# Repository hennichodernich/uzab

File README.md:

# UZAB: Universal Zynq-7000 AD/DA Board
A KiCad project

Presented without any warranty

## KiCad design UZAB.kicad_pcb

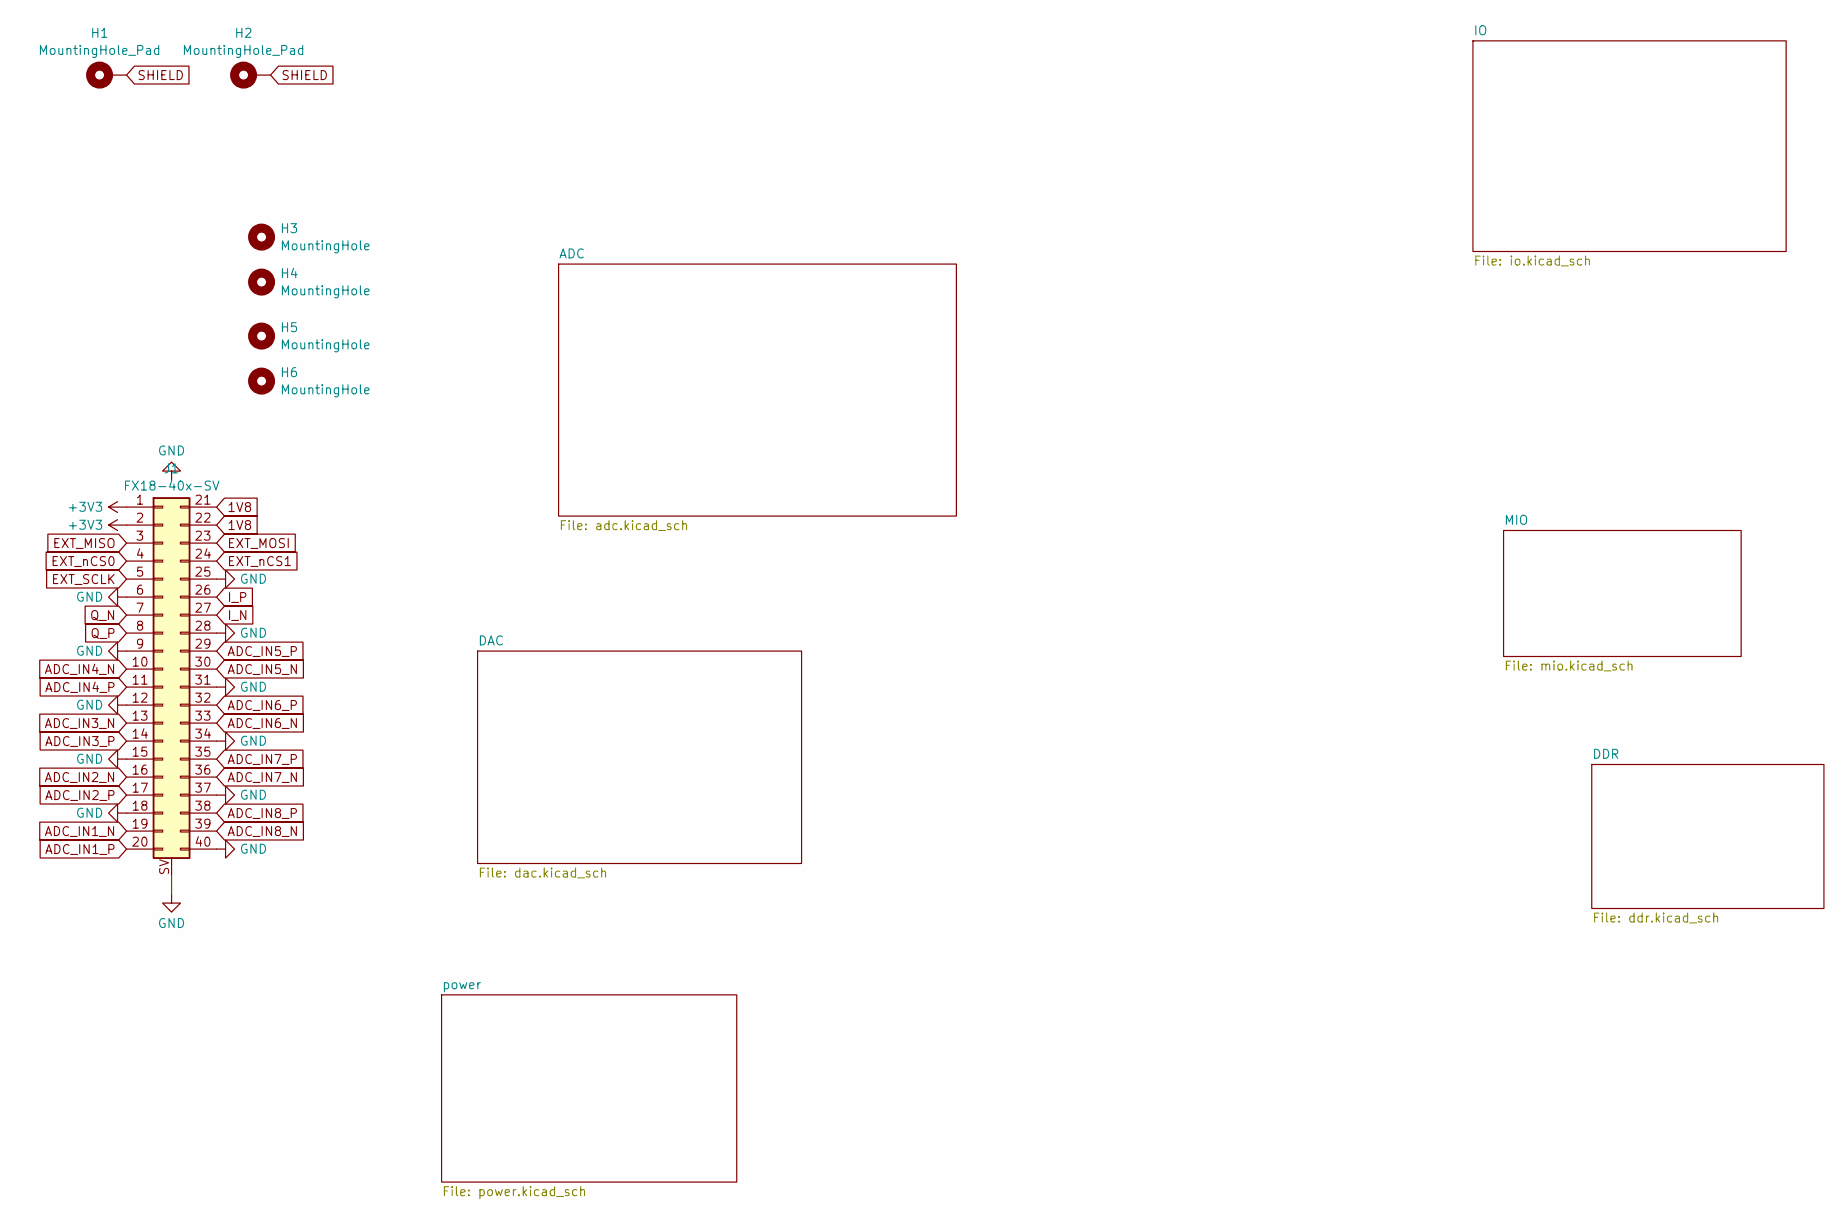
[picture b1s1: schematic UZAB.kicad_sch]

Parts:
H1, H2: MountingHole_Pad; MountingHole_3.2mm_M3_DIN965_Pad_TopBottom
H3, H4, H5, H6: MountingHole; MountingHole_3.2mm_M3_DIN965
J1: FX18-40x-SV; FX18-40P-0.8SV

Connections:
1V8: J1.21, J1.22; also elsewhere on the board
3V3: J1.1, J1.2; also elsewhere on the board
ADC_IN1_N: J1.19; also elsewhere on the board
ADC_IN1_P: J1.20; also elsewhere on the board
ADC_IN2_N: J1.16; also elsewhere on the board
ADC_IN2_P: J1.17; also elsewhere on the board
ADC_IN3_N: J1.13; also elsewhere on the board
ADC_IN3_P: J1.14; also elsewhere on the board
ADC_IN4_N: J1.10; also elsewhere on the board
ADC_IN4_P: J1.11; also elsewhere on the board
ADC_IN5_N: J1.30; also elsewhere on the board
ADC_IN5_P: J1.29; also elsewhere on the board
ADC_IN6_N: J1.33; also elsewhere on the board
ADC_IN6_P: J1.32; also elsewhere on the board
ADC_IN7_N: J1.36; also elsewhere on the board
ADC_IN7_P: J1.35; also elsewhere on the board
ADC_IN8_N: J1.39; also elsewhere on the board
ADC_IN8_P: J1.38; also elsewhere on the board
EXT_MISO: J1.3; also elsewhere on the board
EXT_MOSI: J1.23; also elsewhere on the board
EXT_SCLK: J1.5; also elsewhere on the board
EXT_nCS0: J1.4; also elsewhere on the board
EXT_nCS1: J1.24; also elsewhere on the board
GND: J1.6, J1.9, J1.12, J1.15, J1.18, J1.25, J1.28, J1.31, J1.34, J1.37, J1.40, J1.SV; also elsewhere on the board
I_N: J1.27; also elsewhere on the board
I_P: J1.26; also elsewhere on the board
Q_N: J1.7; also elsewhere on the board
Q_P: J1.8; also elsewhere on the board
SHIELD: H1.1, H2.1; also elsewhere on the board

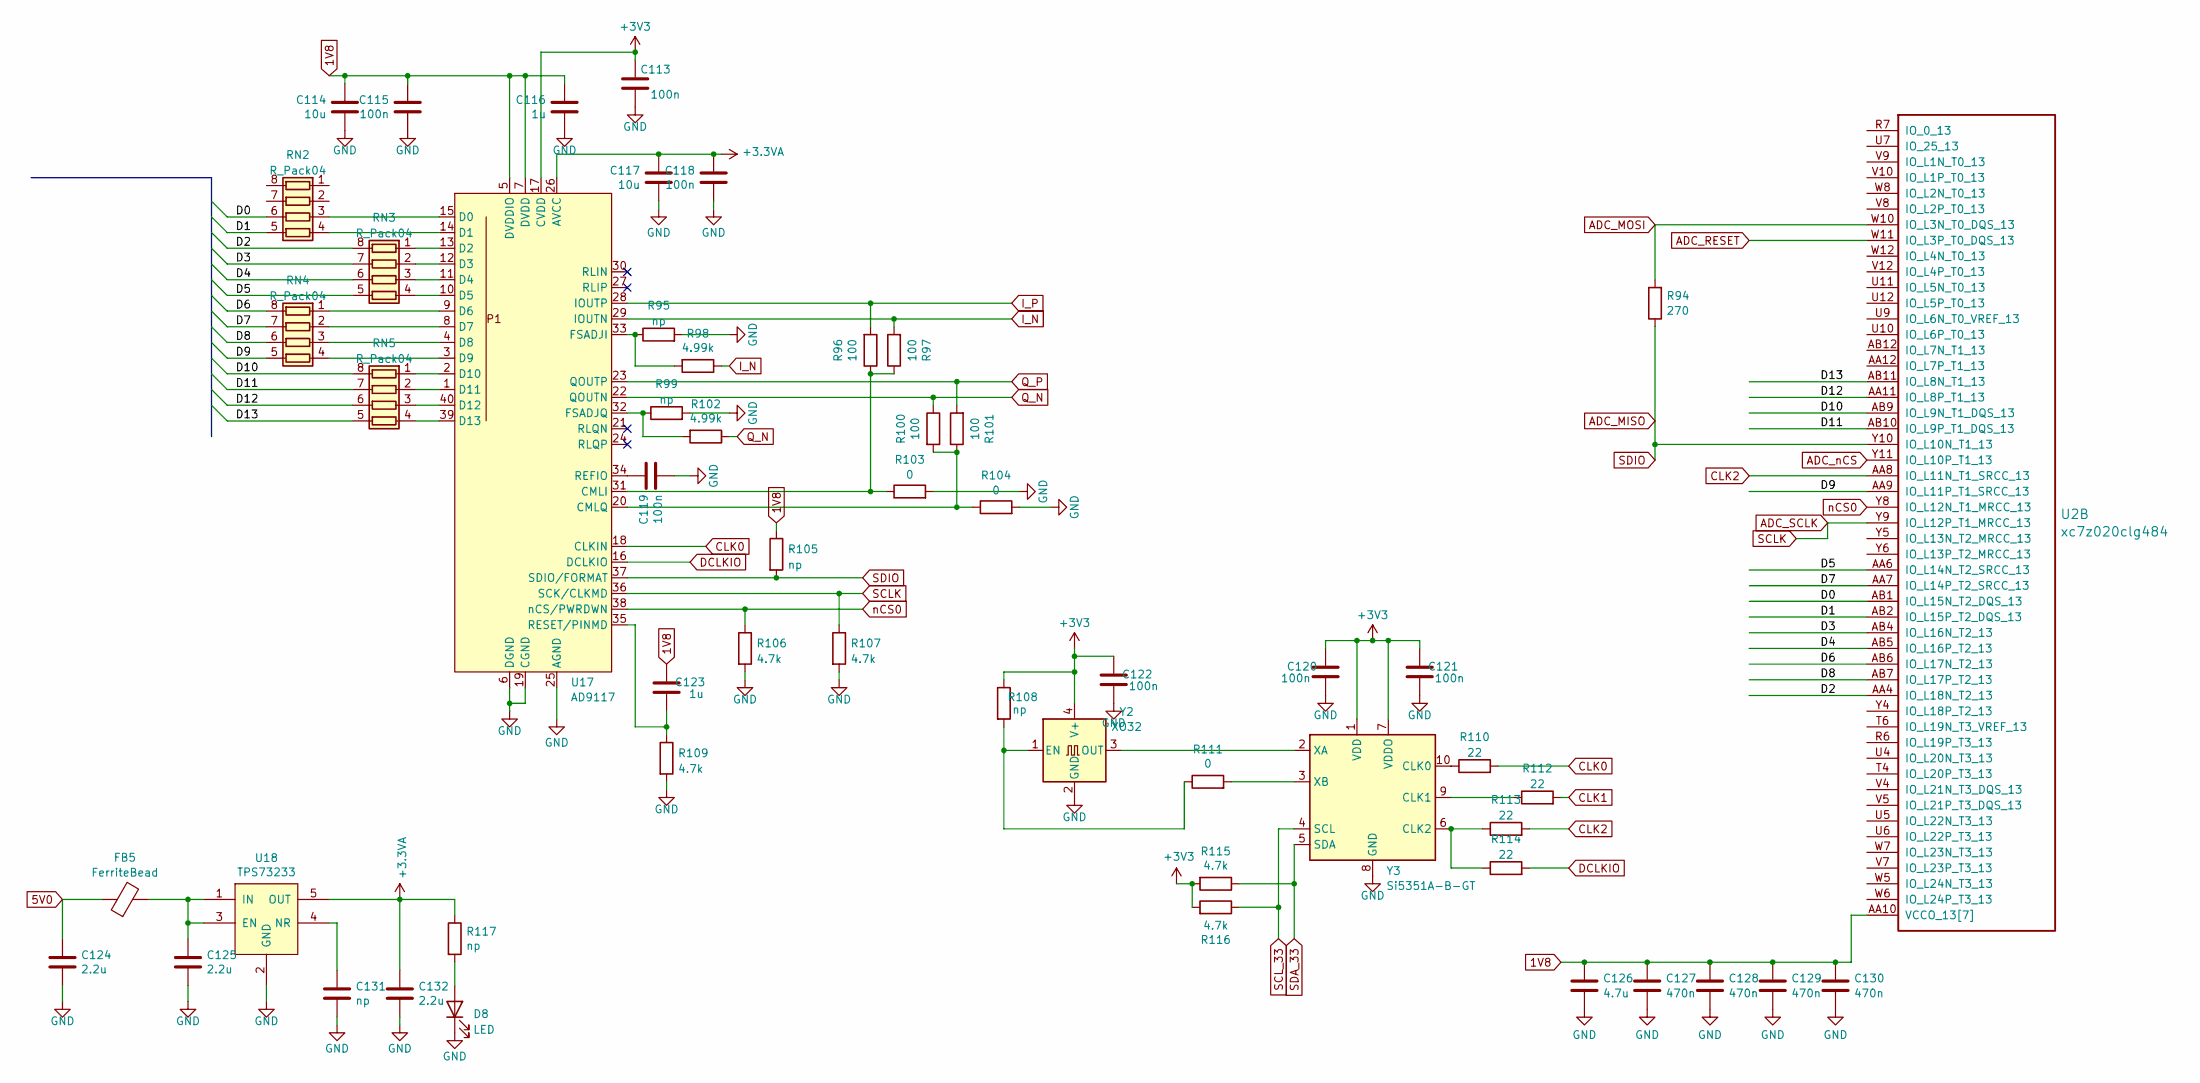
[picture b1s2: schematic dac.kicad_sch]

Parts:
C113, C115, C118, C119, C120, C121, C122: 100n; C_0402_1005Metric
C114, C117: 10u; C_0603_1608Metric
C116: 1u; C_0603_1608Metric
C123: 1u; C_0402_1005Metric
C124, C125, C132: 2.2u; C_0603_1608Metric
C126: 4.7u; C_0603_1608Metric
C127, C128, C129, C130: 470n; C_0201_BGA
C131: np; C_0402_1005Metric
D8: LED; LED_0603_1608Metric
FB5: FerriteBead; L_0603_1608Metric
R94: 270; R_0402_1005Metric
R95, R99, R105, R108: np; R_0402_1005Metric
R96, R97, R100, R101: 100; R_0603_1608Metric
R98, R102: 4.99k; R_0603_1608Metric
R103, R104, R111: 0; R_0402_1005Metric
R106, R107, R109, R115, R116: 4.7k; R_0402_1005Metric
R110, R112, R113, R114: 22; R_0402_1005Metric
R117: np; R_0603_1608Metric
RN2, RN3, RN4, RN5: R_Pack04; R_Array_Concave_4x0603
U2: xc7z020clg484; Xilinx_CLG484_CLG485
U17: AD9117; HVQFN-40-1EP_6x6mm_P0.5mm_EP4.1x4.1mm_ThermalVias
U18: TPS73233; SOT-23-5
Y2: XO32; Oscillator_SMD_EuroQuartz_XO32-4Pin_3.2x2.5mm
Y3: Si5351A-B-GT; MSOP-10_3x3mm_P0.5mm

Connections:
1V8: C114.1, C115.1, C116.1, C123.1, C126.1, C127.1, C128.1, C129.1, C130.1, R105.1, U2.AA10 (VCCO_13[7]), U2.AB3 (VCCO_13[7]), U2.T5 (VCCO_13[7]), U2.U8 (VCCO_13[7]), U2.V11 (VCCO_13[7]), U2.W4 (VCCO_13[7]), U2.Y7 (VCCO_13[7]), U17.5 (DVDDIO), U17.7 (DVDD); also elsewhere on the board
3V3: C113.1, C120.1, C121.1, C122.1, R108.1, R115.2, R116.2, U17.17 (CVDD), Y2.4 (V+), Y3.1 (VDD), Y3.7 (VDDO); also elsewhere on the board
5V0: C124.1, FB5.1; also elsewhere on the board
+3.3VA: C117.1, C118.1, C132.1, R117.1, U17.26 (AVCC), U18.5 (OUT)
/DAC/D0: RN2.6 (R3.2), U2.AB1 (IO_L15N_T2_DQS_13)
/DAC/D1: RN2.5 (R4.2), U2.AB2 (IO_L15P_T2_DQS_13)
/DAC/D2: RN3.8 (R1.2), U2.AA4 (IO_L18N_T2_13)
/DAC/D3: RN3.7 (R2.2), U2.AB4 (IO_L16N_T2_13)
/DAC/D4: RN3.6 (R3.2), U2.AB5 (IO_L16P_T2_13)
/DAC/D5: RN3.5 (R4.2), U2.AA6 (IO_L14N_T2_SRCC_13)
/DAC/D6: RN4.8 (R1.2), U2.AB6 (IO_L17N_T2_13)
/DAC/D7: RN4.7 (R2.2), U2.AA7 (IO_L14P_T2_SRCC_13)
/DAC/D8: RN4.6 (R3.2), U2.AB7 (IO_L17P_T2_13)
/DAC/D9: RN4.5 (R4.2), U2.AA9 (IO_L11P_T1_SRCC_13)
/DAC/D10: RN5.8 (R1.2), U2.AB9 (IO_L9N_T1_DQS_13)
/DAC/D11: RN5.7 (R2.2), U2.AB10 (IO_L9P_T1_DQS_13)
/DAC/D12: RN5.6 (R3.2), U2.AA11 (IO_L8P_T1_13)
/DAC/D13: RN5.5 (R4.2), U2.AB11 (IO_L8N_T1_13)
ADC_MISO: R94.1, R105.2, U2.Y10 (IO_L10N_T1_13), U17.37 (SDIO/FORMAT); also elsewhere on the board
ADC_MOSI: R94.2, U2.W10 (IO_L3N_T0_DQS_13); also elsewhere on the board
ADC_RESET: U2.W11 (IO_L3P_T0_DQS_13); also elsewhere on the board
ADC_SCLK: R107.1, U2.Y9 (IO_L12P_T1_MRCC_13), U17.36 (SCK/CLKMD); also elsewhere on the board
ADC_nCS: U2.Y11 (IO_L10P_T1_13); also elsewhere on the board
CLK0: R110.2, U17.18 (CLKIN)
CLK1: R112.2; also elsewhere on the board
CLK2: R113.2, U2.AA8 (IO_L11N_T1_SRCC_13)
DCLKIO: R114.2, U17.16 (DCLKIO)
GND: C113.2, C114.2, C115.2, C116.2, C117.2, C118.2, C119.2, C120.2, C121.2, C122.2, C124.2, C125.2, C126.2, C127.2, C128.2, C129.2, C130.2, C131.2, C132.2, D8.1 (K), R95.2, R99.2, R103.2, R104.2, R106.2, R107.2, R109.2, U17.6 (DGND), U17.19 (CGND), U17.25 (AGND), U17.41 (AGND), U18.2 (GND), Y2.2 (GND), Y3.8 (GND); also elsewhere on the board
I_N: R97.2, R98.1, U17.29 (IOUTN); also elsewhere on the board
I_P: R96.2, U17.28 (IOUTP); also elsewhere on the board
unnamed: D8.2 (A), R117.2
unnamed: RN2.3 (R3.1), U17.15 (D0)
unnamed: RN2.4 (R4.1), U17.14 (D1)
unnamed: RN3.1 (R1.1), U17.13 (D2)
unnamed: RN3.2 (R2.1), U17.12 (D3)
unnamed: RN3.3 (R3.1), U17.11 (D4)
unnamed: RN3.4 (R4.1), U17.10 (D5)
unnamed: RN4.1 (R1.1), U17.9 (D6)
unnamed: RN4.2 (R2.1), U17.8 (D7)
unnamed: RN4.3 (R3.1), U17.4 (D8)
unnamed: RN4.4 (R4.1), U17.3 (D9)
unnamed: RN5.1 (R1.1), U17.2 (D10)
unnamed: RN5.2 (R2.1), U17.1 (D11)
unnamed: RN5.3 (R3.1), U17.40 (D12)
unnamed: RN5.4 (R4.1), U17.39 (D13)
unnamed: R96.1, R97.1, R103.1, U17.31 (CMLI)
unnamed: R100.2, R101.1, R104.1, U17.20 (CMLQ)
unnamed: R95.1, R98.2, U17.33 (FSADJI)
unnamed: R99.1, R102.2, U17.32 (FSADJQ)
unnamed: C119.1, U17.34 (REFIO)
unnamed: C123.2, R109.1, U17.35 (RESET/PINMD)
unnamed: C125.1, FB5.2, U18.1 (IN), U18.3 (EN)
unnamed: C131.1, U18.4 (NR)
unnamed: R108.2, R111.1, Y2.1 (EN)
unnamed: Y2.3 (OUT), Y3.2 (XA)
unnamed: R110.1, Y3.10 (CLK0)
unnamed: R112.1, Y3.9 (CLK1)
unnamed: R113.1, R114.1, Y3.6 (CLK2)
unnamed: R111.2, Y3.3 (XB)
Q_N: R100.1, R102.1, U17.22 (QOUTN); also elsewhere on the board
Q_P: R101.2, U17.23 (QOUTP); also elsewhere on the board
SCL_33: R116.1, Y3.4 (SCL); also elsewhere on the board
SDA_33: R115.1, Y3.5 (SDA); also elsewhere on the board
nCS0: R106.1, U2.Y8 (IO_L12N_T1_MRCC_13), U17.38 (nCS/PWRDWN)

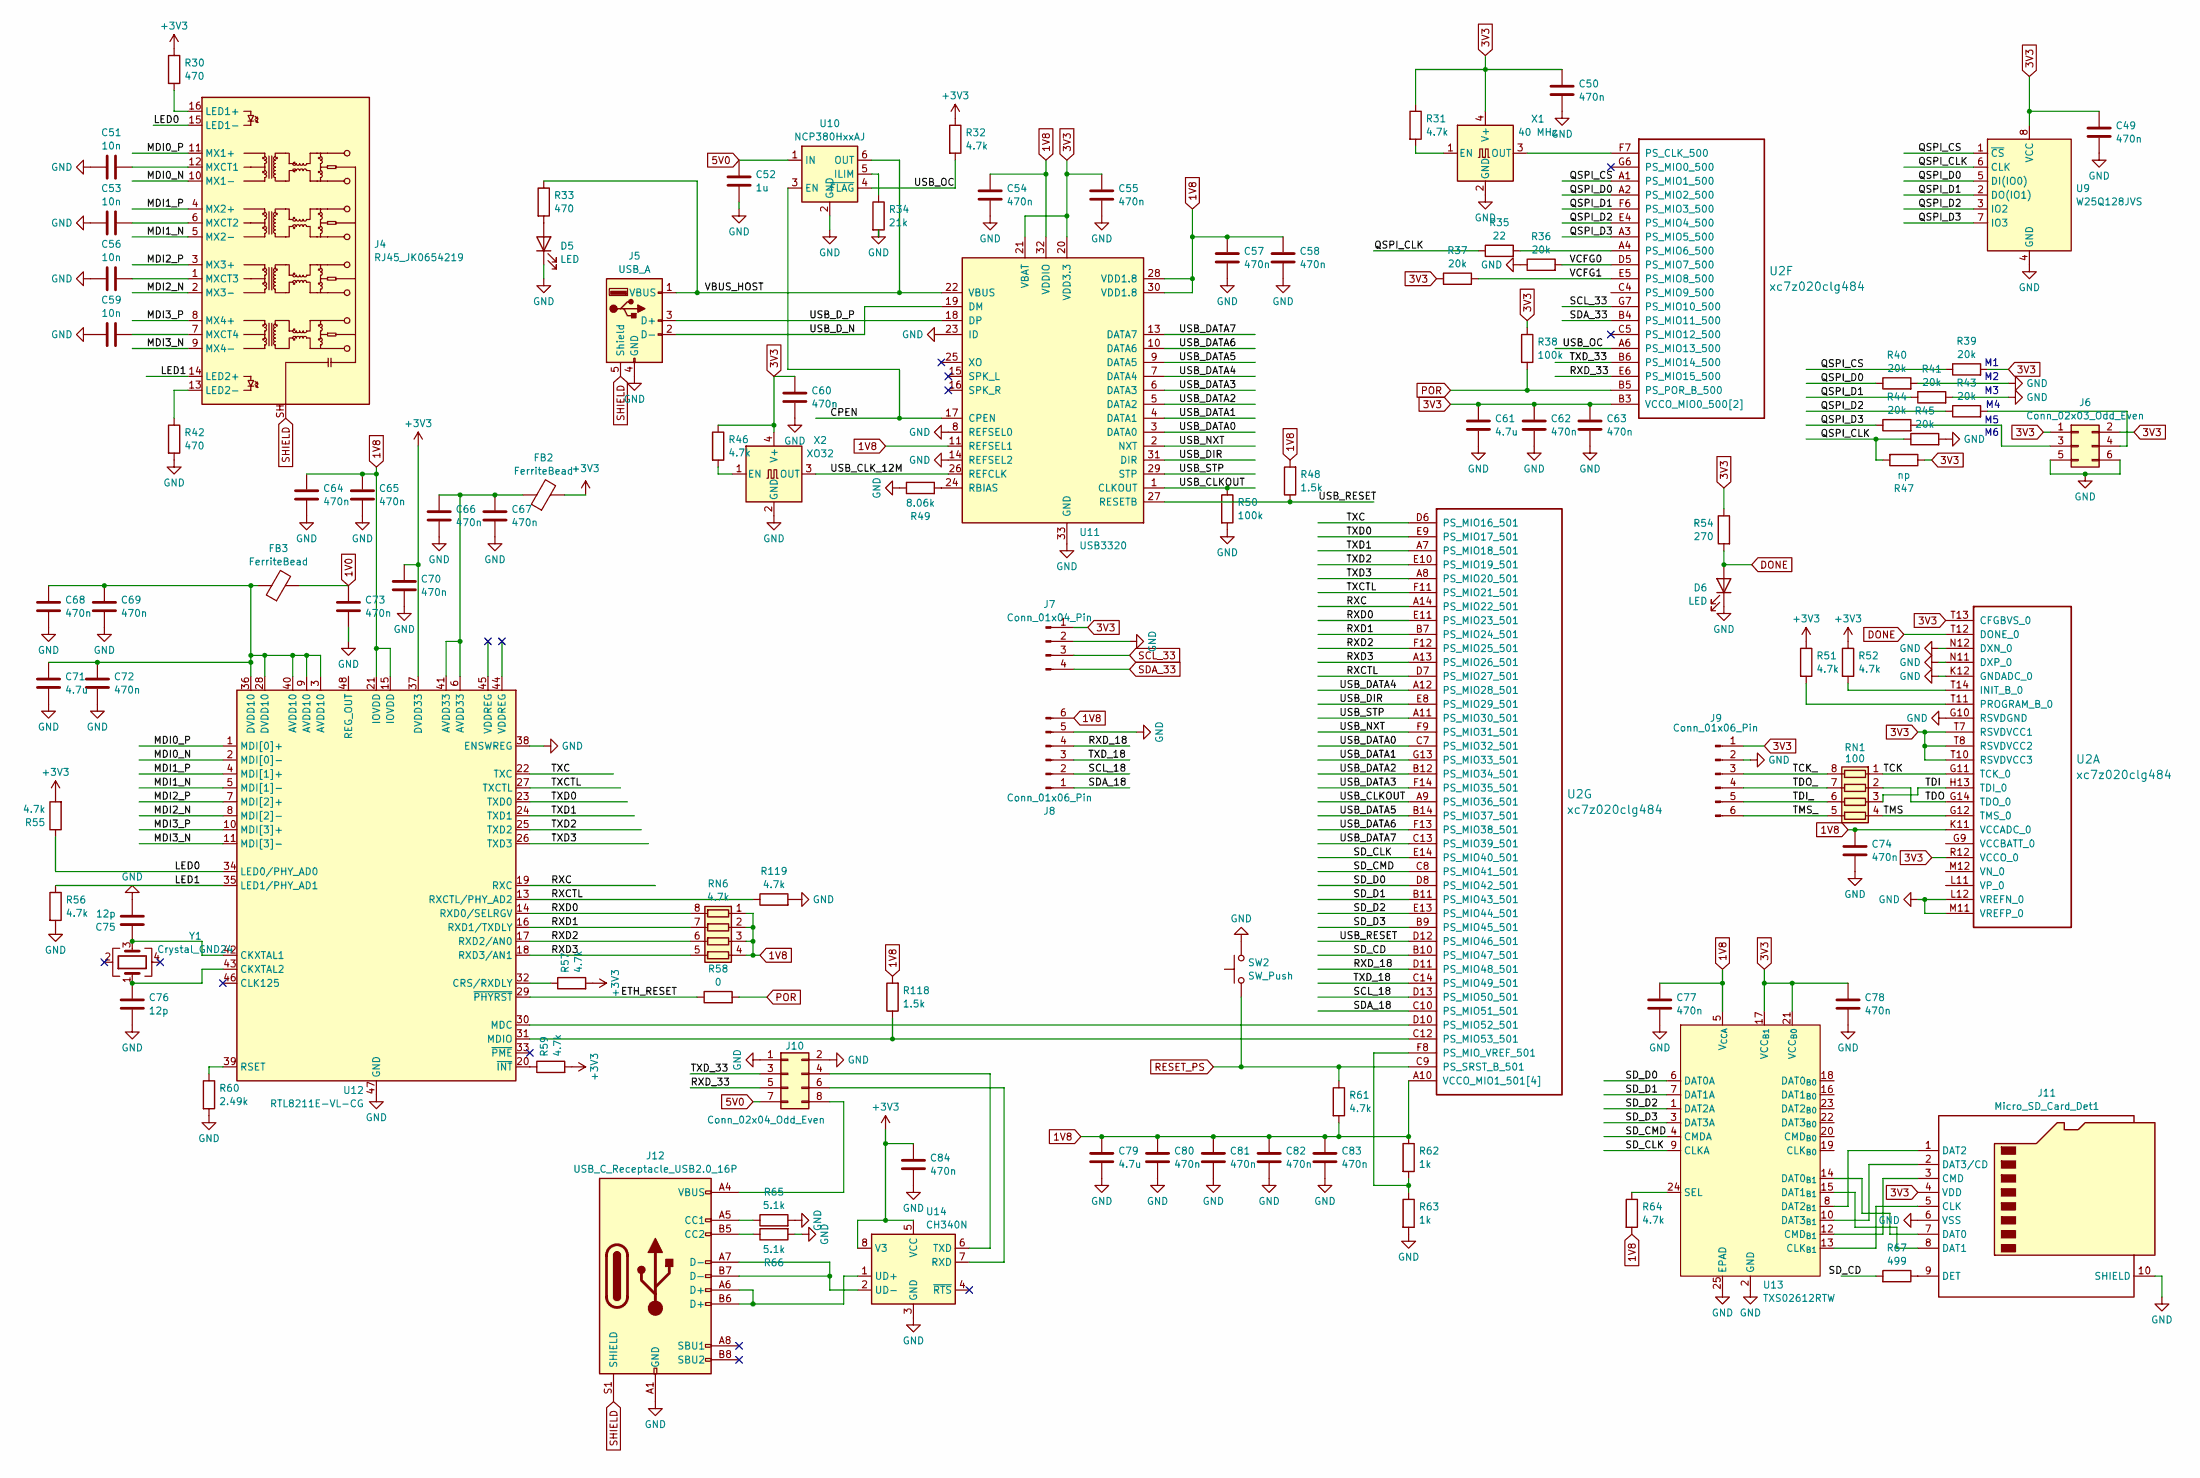
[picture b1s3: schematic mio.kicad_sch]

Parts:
C49, C50, C54, C55, C57, C58, C60, C64, C65, C66, C67, C68, C69, C70, C72, C73, C77, C78, C84: 470n; C_0402_1005Metric
C51, C53, C56, C59: 10n; C_0402_1005Metric
C52: 1u; C_0603_1608Metric
C61, C71, C79: 4.7u; C_0603_1608Metric
C62, C63, C74, C80, C81, C82, C83: 470n; C_0201_BGA
C75, C76: 12p; C_0402_1005Metric
D5, D6: LED; LED_0603_1608Metric
FB2, FB3: FerriteBead; L_0603_1608Metric
J4: RJ45_JK0654219; RJ45_Pulse_JK0654219NL_Horizontal
J5: USB_A; USB_A_Wuerth_614004134726_Horizontal
J6: Conn_02x03_Odd_Even; PinHeader_2x03_P2.54mm_Vertical
J7: Conn_01x04_Pin; PinHeader_1x04_P2.54mm_Vertical
J8, J9: Conn_01x06_Pin; PinHeader_1x06_P2.54mm_Vertical
J10: Conn_02x04_Odd_Even; PinHeader_2x04_P2.54mm_Vertical
J11: Micro_SD_Card_Det1; EBAZ_SD
J12: USB_C_Receptacle_USB2.0_16P; USB_C_Receptacle_HRO_TYPE-C-31-M-12
R30, R42: 470; R_0402_1005Metric
R31, R32, R46, R51, R52, R55, R56, R57, R59, R61, R64, R119: 4.7k; R_0402_1005Metric
R33: 470; R_0603_1608Metric
R34: 21k; R_0402_1005Metric
R35: 22; R_0402_1005Metric
R36, R37, R39, R40, R41, R43, R44, R45: 20k; R_0402_1005Metric
R38, R50: 100k; R_0402_1005Metric
R47: np; R_0402_1005Metric
R48, R118: 1.5k; R_0402_1005Metric
R49: 8.06k; R_0603_1608Metric
R54: 270; R_0603_1608Metric
R58: 0; R_0402_1005Metric
R60: 2.49k; R_0402_1005Metric
R62, R63: 1k; R_0402_BGA_Diag
R65, R66: 5.1k; R_0402_1005Metric
R67: 499; R_0402_1005Metric
RN1: 100; R_Array_Concave_4x0402
RN6: 4.7k; R_Array_Concave_4x0603
SW2: SW_Push; SW_Push_SPST_NO_Xunpu_TS-1088
U2: xc7z020clg484; Xilinx_CLG484_CLG485
U9: W25Q128JVS; SOIC-8_5.3x5.3mm_P1.27mm
U10: NCP380HxxAJ; TSOP-6_1.65x3.05mm_P0.95mm
U11: USB3320; QFN-32-1EP_5x5mm_P0.5mm_EP3.3x3.3mm_ThermalVias
U12: RTL8211E-VL-CG; QFN-48-1EP_6x6mm_P0.4mm_EP4.3x4.3mm_ThermalVias
U13: TXS02612RTW; WQFN-24-1EP_4x4mm_P0.5mm_EP2.45x2.45mm_ThermalVias
U14: CH340N; SOIC-8_3.9x4.9mm_P1.27mm
X1: 40 MHz; Oscillator_SMD_EuroQuartz_XO53-4Pin_5.0x3.2mm
X2: XO32; Oscillator_SMD_EuroQuartz_XO32-4Pin_3.2x2.5mm
Y1: Crystal_GND24; Crystal_SMD_3225-4Pin_3.2x2.5mm

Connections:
1V0: C73.1, FB3.2; also elsewhere on the board
1V8: C54.1, C57.1, C58.1, C64.1, C65.1, C74.1, C77.1, C79.1, C80.1, C81.1, C82.1, C83.1, J8.6, R48.2, R61.2, R62.1, R64.2, R118.2, RN6.1 (R1.1), RN6.2 (R2.1), RN6.3 (R3.1), RN6.4 (R4.1), U2.A10 (VCCO_MIO1_501[4]), U2.B13 (VCCO_MIO1_501[4]), U2.D9 (VCCO_MIO1_501[4]), U2.E12 (VCCO_MIO1_501[4]), U2.K11 (VCCADC_0), U11.11 (REFSEL1), U11.28 (VDD1.8), U11.30 (VDD1.8), U11.32 (VDDIO), U12.15 (IOVDD), U12.21 (IOVDD), U13.5 (V_{CCA}); also elsewhere on the board
3V3: C49.1, C50.1, C55.1, C60.1, C61.1, C62.1, C63.1, C70.1, C78.1, C84.1, FB2.2, J6.1, J6.2, J7.1, J9.1, J11.4 (VDD), R30.1, R31.1, R32.1, R37.1, R38.1, R39.2, R46.1, R47.1, R51.1, R52.1, R54.1, R55.2, R57.2, R59.2, U2.B3 (VCCO_MIO0_500[2]), U2.C6 (VCCO_MIO0_500[2]), U2.R12 (VCCO_0), U2.T7 (RSVDVCC1), U2.T8 (RSVDVCC2), U2.T10 (RSVDVCC3), U2.T13 (CFGBVS_0), U9.8 (VCC), U11.20 (VDD3.3), U11.21 (VBAT), U12.37 (DVDD33), U13.17 (VCC_{B1}), U13.21 (VCC_{B0}), U14.5 (VCC), U14.8 (V3), X1.4 (V+), X2.4 (V+); also elsewhere on the board
5V0: C52.1, J10.7, U10.1 (IN); also elsewhere on the board
/MIO/CPEN: U10.3 (EN), U11.17 (CPEN)
/MIO/ETH_RESET: R58.1, U12.29 (~PHYRST)
/MIO/LED0: J4.15 (LED1-), R55.1, U12.34 (LED0/PHY_AD0)
/MIO/LED1: J4.14 (LED2+), R56.1, U12.35 (LED1/PHY_AD1)
/MIO/MDI0_N: J4.10 (MX1-), U12.2 (MDI[0]-)
/MIO/MDI0_P: J4.11 (MX1+), U12.1 (MDI[0]+)
/MIO/MDI1_N: J4.5 (MX2-), U12.5 (MDI[1]-)
/MIO/MDI1_P: J4.4 (MX2+), U12.4 (MDI[1]+)
/MIO/MDI2_N: J4.2 (MX3-), U12.8 (MDI[2]-)
/MIO/MDI2_P: J4.3 (MX3+), U12.7 (MDI[2]+)
/MIO/MDI3_N: J4.9 (MX4-), U12.11 (MDI[3]-)
/MIO/MDI3_P: J4.8 (MX4+), U12.10 (MDI[3]+)
/MIO/QSPI_CLK: R35.1, R45.1, R47.2, U9.6 (CLK)
/MIO/QSPI_CS: R39.1, U2.A1 (PS_MIO1_500), U9.1 (~CS)
/MIO/QSPI_D0: R40.1, U2.A2 (PS_MIO2_500), U9.5 (DI(IO0))
/MIO/QSPI_D1: R41.1, U2.F6 (PS_MIO3_500), U9.2 (DO(IO1))
/MIO/QSPI_D2: R43.1, U2.E4 (PS_MIO4_500), U9.3 (IO2)
/MIO/QSPI_D3: R44.1, U2.A3 (PS_MIO5_500), U9.7 (IO3)
/MIO/RXC: U2.A14 (PS_MIO22_501), U12.19 (RXC)
/MIO/RXCTL: R119.1, U2.D7 (PS_MIO27_501), U12.13 (RXCTL/PHY_AD2)
/MIO/RXD0: RN6.8 (R1.2), U2.E11 (PS_MIO23_501), U12.14 (RXD0/SELRGV)
/MIO/RXD1: RN6.7 (R2.2), U2.B7 (PS_MIO24_501), U12.16 (RXD1/TXDLY)
/MIO/RXD2: RN6.6 (R3.2), U2.F12 (PS_MIO25_501), U12.17 (RXD2/AN0)
/MIO/RXD3: RN6.5 (R4.2), U2.A13 (PS_MIO26_501), U12.18 (RXD3/AN1)
/MIO/RXD_18: J8.4, U2.D11 (PS_MIO48_501)
/MIO/RXD_33: J10.5, U2.E6 (PS_MIO15_500)
/MIO/SCL_18: J8.2, U2.D13 (PS_MIO50_501)
/MIO/SDA_18: J8.1, U2.C10 (PS_MIO51_501)
/MIO/SD_CD: R67.2, U2.B10 (PS_MIO47_501)
/MIO/SD_CLK: U2.E14 (PS_MIO40_501), U13.9 (CLKA)
/MIO/SD_CMD: U2.C8 (PS_MIO41_501), U13.4 (CMDA)
/MIO/SD_D0: U2.D8 (PS_MIO42_501), U13.6 (DAT0A)
/MIO/SD_D1: U2.B11 (PS_MIO43_501), U13.7 (DAT1A)
/MIO/SD_D2: U2.E13 (PS_MIO44_501), U13.1 (DAT2A)
/MIO/SD_D3: U2.B9 (PS_MIO45_501), U13.3 (DAT3A)
/MIO/TCK: RN1.1 (R1.1), U2.G11 (TCK_0)
/MIO/TCK_: J9.3, RN1.8 (R1.2)
/MIO/TDI: RN1.3 (R3.1), U2.H13 (TDI_0)
/MIO/TDI_: J9.5, RN1.6 (R3.2)
/MIO/TDO: RN1.2 (R2.1), U2.G14 (TDO_0)
/MIO/TDO_: J9.4, RN1.7 (R2.2)
/MIO/TMS: RN1.4 (R4.1), U2.G12 (TMS_0)
/MIO/TMS_: J9.6, RN1.5 (R4.2)
/MIO/TXC: U2.D6 (PS_MIO16_501), U12.22 (TXC)
/MIO/TXCTL: U2.F11 (PS_MIO21_501), U12.27 (TXCTL)
/MIO/TXD0: U2.E9 (PS_MIO17_501), U12.23 (TXD0)
/MIO/TXD1: U2.A7 (PS_MIO18_501), U12.24 (TXD1)
/MIO/TXD2: U2.E10 (PS_MIO19_501), U12.25 (TXD2)
/MIO/TXD3: U2.A8 (PS_MIO20_501), U12.26 (TXD3)
/MIO/TXD_18: J8.3, U2.C14 (PS_MIO49_501)
/MIO/TXD_33: J10.3, U2.B6 (PS_MIO14_500)
/MIO/USB_CLKOUT: R50.1, U2.A9 (PS_MIO36_501), U11.1 (CLKOUT)
/MIO/USB_CLK_12M: U11.26 (REFCLK), X2.3 (OUT)
/MIO/USB_DATA0: U2.C7 (PS_MIO32_501), U11.3 (DATA0)
/MIO/USB_DATA1: U2.G13 (PS_MIO33_501), U11.4 (DATA1)
/MIO/USB_DATA2: U2.B12 (PS_MIO34_501), U11.5 (DATA2)
/MIO/USB_DATA3: U2.F14 (PS_MIO35_501), U11.6 (DATA3)
/MIO/USB_DATA4: U2.A12 (PS_MIO28_501), U11.7 (DATA4)
/MIO/USB_DATA5: U2.B14 (PS_MIO37_501), U11.9 (DATA5)
/MIO/USB_DATA6: U2.F13 (PS_MIO38_501), U11.10 (DATA6)
/MIO/USB_DATA7: U2.C13 (PS_MIO39_501), U11.13 (DATA7)
/MIO/USB_DIR: U2.E8 (PS_MIO29_501), U11.31 (DIR)
/MIO/USB_D_N: J5.2 (D-), U11.19 (DM)
/MIO/USB_D_P: J5.3 (D+), U11.18 (DP)
/MIO/USB_NXT: U2.F9 (PS_MIO31_501), U11.2 (NXT)
/MIO/USB_OC: R32.2, U2.A6 (PS_MIO13_500), U10.4 (~FLAG)
/MIO/USB_RESET: R48.1, U2.D12 (PS_MIO46_501), U11.27 (RESETB)
/MIO/USB_STP: U2.A11 (PS_MIO30_501), U11.29 (STP)
/MIO/VBUS_HOST: J5.1 (VBUS), R33.1, U10.6 (OUT), U11.22 (VBUS)
/MIO/VCFG0: R36.2, U2.D5 (PS_MIO7_500)
/MIO/VCFG1: R37.2, U2.E5 (PS_MIO8_500)
DONE: D6.2 (A), R54.2, U2.T12 (DONE_0)
GND: C49.2, C50.2, C51.1, C52.2, C53.1, C54.2, C55.2, C56.1, C57.2, C58.2, C59.1, C60.2, C61.2, C62.2, C63.2, C64.2, C65.2, C66.2, C67.2, C68.1, C69.1, C70.2, C71.1, C72.1, C73.2, C74.2, C75.2, C76.2, C77.2, C78.2, C79.2, C80.2, C81.2, C82.2, C83.2, C84.2, D5.1 (K), D6.1 (K), J5.4 (GND), J6.5, J6.6, J7.2, J8.5, J9.2, J10.1, J10.2, J11.6 (VSS), J11.10 (SHIELD), J11.11 (SHIELD), J11.12 (SHIELD), J11.13 (SHIELD), J12.A1 (GND), J12.A12 (GND), J12.B1 (GND), J12.B12 (GND), R34.2, R36.1, R40.2, R41.2, R42.2, R45.2, R49.1, R50.2, R56.2, R60.2, R63.2, R65.2, R66.2, R119.2, SW2.2, U2.G10 (RSVDGND), U2.K12 (GNDADC_0), U2.L12 (VREFN_0), U2.M11 (VREFP_0), U2.N11 (DXP_0), U2.N12 (DXN_0), U9.4 (GND), U10.2 (GND), U11.8 (REFSEL0), U11.14 (REFSEL2), U11.23 (ID), U11.33 (GND), U12.38 (ENSWREG), U12.47 (GND), U12.49 (GND), U13.2 (GND), U13.11 (GND), U13.25 (EPAD), U14.3 (GND), X1.2 (GND), X2.2 (GND); also elsewhere on the board
unnamed: C66.1, C67.1, FB2.1, U12.6 (AVDD33), U12.41 (AVDD33)
unnamed: C68.2, C69.2, C71.2, C72.2, FB3.1, U12.3 (AVDD10), U12.9 (AVDD10), U12.28 (DVDD10), U12.36 (DVDD10), U12.40 (AVDD10)
unnamed: D5.2 (A), R33.2
unnamed: J4.16 (LED1+), R30.2
unnamed: J4.13 (LED2-), R42.1
unnamed: C51.2, J4.12 (MXCT1)
unnamed: C53.2, J4.6 (MXCT2)
unnamed: C56.2, J4.1 (MXCT3)
unnamed: C59.2, J4.7 (MXCT4)
unnamed: J6.3, R44.2
unnamed: J6.4, R43.2
unnamed: J10.4, U14.6 (TXD)
unnamed: J10.6, U14.7 (RXD)
unnamed: J10.8, J12.A4 (VBUS), J12.A9 (VBUS), J12.B4 (VBUS), J12.B9 (VBUS)
unnamed: J11.5 (CLK), U13.13 (CLK_{B1})
unnamed: J11.3 (CMD), U13.12 (CMD_{B1})
unnamed: J11.7 (DAT0), U13.14 (DAT0_{B1})
unnamed: J11.8 (DAT1), U13.15 (DAT1_{B1})
unnamed: J11.1 (DAT2), U13.8 (DAT2_{B1})
unnamed: J11.2 (DAT3/CD), U13.10 (DAT3_{B1})
unnamed: J11.9 (DET), R67.1
unnamed: J12.A5 (CC1), R65.1
unnamed: J12.B5 (CC2), R66.1
unnamed: R52.2, U2.T14 (INIT_B_0)
unnamed: R51.2, U2.T11 (PROGRAM_B_0)
unnamed: U2.F7 (PS_CLK_500), X1.3 (OUT)
unnamed: R35.2, U2.A4 (PS_MIO6_500)
unnamed: R62.2, R63.1, U2.F8 (PS_MIO_VREF_501)
unnamed: R34.1, U10.5 (ILIM)
unnamed: R49.2, U11.24 (RBIAS)
unnamed: C75.1, U12.42 (CKXTAL1), Y1.3
unnamed: C76.1, U12.43 (CKXTAL2), Y1.1
unnamed: R57.1, U12.32 (CRS/RXDLY)
unnamed: U2.D10 (PS_MIO52_501), U12.30 (MDC)
unnamed: R118.1, U2.C12 (PS_MIO53_501), U12.31 (MDIO)
unnamed: R60.1, U12.39 (RSET)
unnamed: R59.1, U12.20 (~INT)
unnamed: R64.1, U13.24 (SEL)
unnamed: J12.A6 (D+), J12.B6 (D+), U14.1 (UD+)
unnamed: J12.A7 (D-), J12.B7 (D-), U14.2 (UD-)
unnamed: R31.2, X1.1 (EN)
unnamed: R46.2, X2.1 (EN)
POR: R38.2, R58.2, U2.B5 (PS_POR_B_500); also elsewhere on the board
RESET_PS: R61.1, SW2.1, U2.C9 (PS_SRST_B_501)
SCL_33: J7.3, U2.G7 (PS_MIO10_500); also elsewhere on the board
SDA_33: J7.4, U2.B4 (PS_MIO11_500); also elsewhere on the board
SHIELD: J4.SH, J5.5 (Shield), J12.S1 (SHIELD); also elsewhere on the board

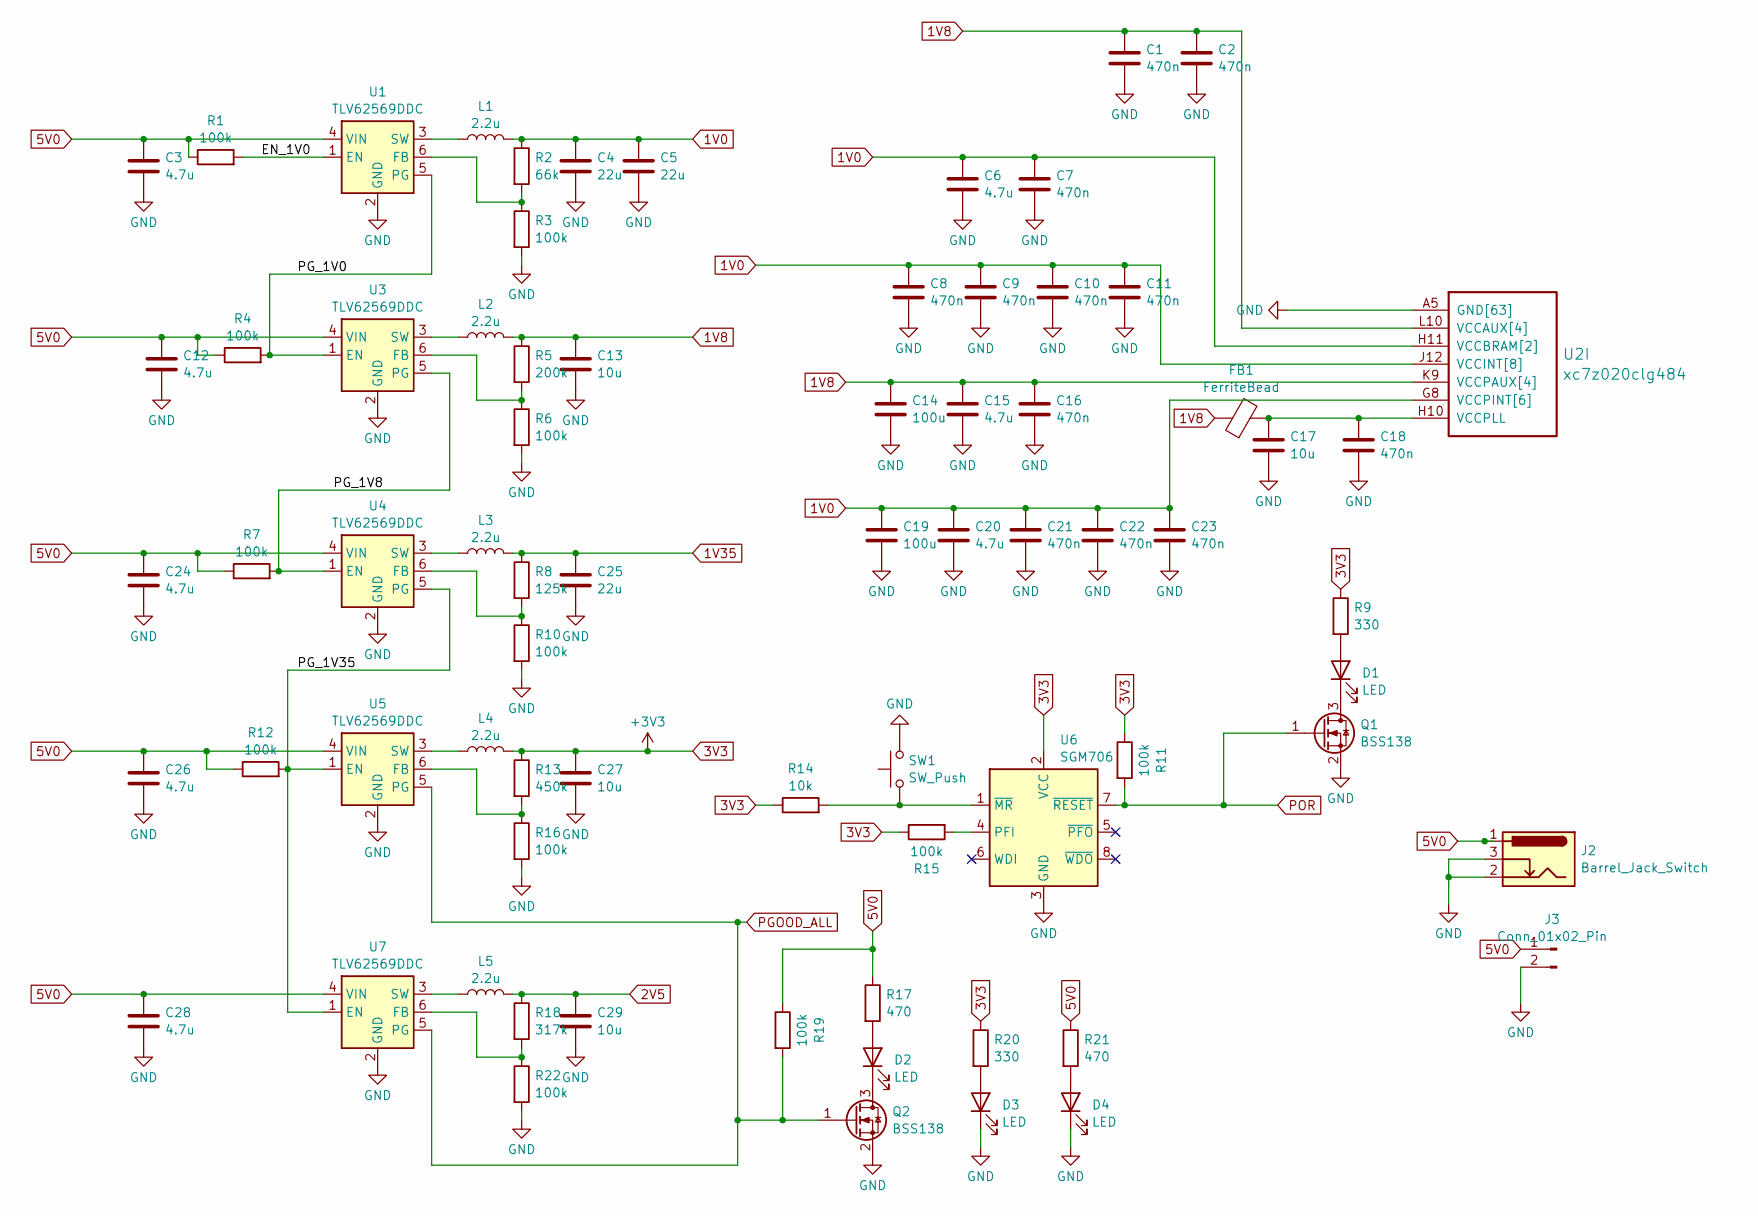
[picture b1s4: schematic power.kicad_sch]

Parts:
C1, C2, C7, C8, C9, C10, C11, C16, C18, C21, C22, C23: 470n; C_0201_BGA
C3, C12, C24, C26, C28: 4.7u; C_0805_2012Metric
C4, C5, C25: 22u; C_0805_2012Metric
C6, C20: 4.7u; C_0603_1608Metric
C13, C27, C29: 10u; C_0805_2012Metric
C14: 100u; C_1206_3216Metric
C15: 4.7u; C_0603_BGA
C17: 10u; C_0603_1608Metric
C19: 100u; C_1206_BGA
D1, D2, D3, D4: LED; LED_0603_1608Metric
FB1: FerriteBead; L_0603_1608Metric
J2: Barrel_Jack_Switch; BarrelJack_Horizontal
J3: Conn_01x02_Pin; JST_XH_B2B-XH-A_1x02_P2.50mm_Vertical
L1, L2, L3, L4, L5: 2.2u; L_Vishay_IHLP-2020
Q1, Q2: BSS138; SOT-23
R1, R3, R4, R6, R7, R10, R12, R16, R22: 100k; R_0603_1608Metric
R2: 66k; R_0603_1608Metric
R5: 200k; R_0603_1608Metric
R8: 125k; R_0603_1608Metric
R9, R20: 330; R_0603_1608Metric
R11, R15, R19: 100k; C_0603_1608Metric
R13: 450k; R_0603_1608Metric
R14: 10k; C_0603_1608Metric
R17, R21: 470; R_0603_1608Metric
R18: 317k; R_0603_1608Metric
SW1: SW_Push; SW_Push_SPST_NO_Xunpu_TS-1088
U1, U3, U4, U5, U7: TLV62569DDC; SOT-23-6
U2: xc7z020clg484; Xilinx_CLG484_CLG485
U6: SGM706; SOIC-8_3.9x4.9mm_P1.27mm

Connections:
1V0: C4.1, C5.1, C6.1, C7.1, C8.1, C9.1, C10.1, C11.1, C19.1, C20.1, C21.1, C22.1, C23.1, L1.2, R2.1, U2.G8 (VCCPINT[6]), U2.H9 (VCCPINT[6]), U2.H11 (VCCBRAM[2]), U2.J8 (VCCPINT[6]), U2.J10 (VCCBRAM[2]), U2.J12 (VCCINT[8]), U2.J14 (VCCINT[8]), U2.K13 (VCCINT[8]), U2.L8 (VCCPINT[6]), U2.L14 (VCCINT[8]), U2.M13 (VCCINT[8]), U2.N8 (VCCPINT[6]), U2.N14 (VCCINT[8]), U2.P13 (VCCINT[8]), U2.R8 (VCCPINT[6]), U2.R14 (VCCINT[8]); also elsewhere on the board
1V8: C1.1, C2.1, C13.1, C14.1, C15.1, C16.1, FB1.1, L2.2, R5.1, U2.K9 (VCCPAUX[4]), U2.L10 (VCCAUX[4]), U2.M9 (VCCPAUX[4]), U2.N10 (VCCAUX[4]), U2.P9 (VCCPAUX[4]), U2.P11 (VCCAUX[4]), U2.R10 (VCCAUX[4]), U2.T9 (VCCPAUX[4]); also elsewhere on the board
1V35: C25.1, L3.2, R8.1; also elsewhere on the board
2V5: C29.1, L5.2, R18.1; also elsewhere on the board
3V3: C27.1, L4.2, R9.1, R11.1, R13.1, R14.1, R15.1, R20.1, U6.2 (VCC); also elsewhere on the board
5V0: C3.1, C12.1, C24.1, C26.1, C28.1, J2.1, J3.1, R1.1, R4.1, R7.1, R12.1, R17.1, R19.1, R21.1, U1.4 (VIN), U3.4 (VIN), U4.4 (VIN), U5.4 (VIN), U7.4 (VIN); also elsewhere on the board
/power/EN_1V0: R1.2, U1.1 (EN)
/power/PG_1V0: R4.2, U1.5 (PG), U3.1 (EN)
/power/PG_1V8: R7.2, U3.5 (PG), U4.1 (EN)
/power/PG_1V35: R12.2, U4.5 (PG), U5.1 (EN), U7.1 (EN)
GND: C1.2, C2.2, C3.2, C4.2, C5.2, C6.2, C7.2, C8.2, C9.2, C10.2, C11.2, C12.2, C13.2, C14.2, C15.2, C16.2, C17.2, C18.2, C19.2, C20.2, C21.2, C22.2, C23.2, C24.2, C25.2, C26.2, C27.2, C28.2, C29.2, D3.1 (K), D4.1 (K), J2.2, J2.3, J3.2, Q1.2 (S), Q2.2 (S), R3.2, R6.2, R10.2, R16.2, R22.2, SW1.2, U1.2 (GND), U2.A5 (GND[63]), U2.A15 (GND[63]), U2.AA5 (GND[63]), U2.AA15 (GND[63]), U2.AB8 (GND[63]), U2.AB18 (GND[63]), U2.B8 (GND[63]), U2.B18 (GND[63]), U2.C1 (GND[63]), U2.C11 (GND[63]), U2.C21 (GND[63]), U2.D4 (GND[63]), U2.D14 (GND[63]), U2.E7 (GND[63]), U2.E17 (GND[63]), U2.F10 (GND[63]), U2.F20 (GND[63]), U2.G3 (GND[63]), U2.H6 (GND[63]), U2.H8 (GND[63]), U2.H12 (GND[63]), U2.H14 (GND[63]), U2.H16 (GND[63]), U2.J9 (GND[63]), U2.J11 (GND[63]), U2.J13 (GND[63]), U2.J19 (GND[63]), U2.K2 (GND[63]), U2.K8 (GND[63]), U2.K10 (GND[63]), U2.K14 (GND[63]), U2.K22 (GND[63]), U2.L5 (GND[63]), U2.L9 (GND[63]), U2.L13 (GND[63]), U2.L15 (GND[63]), U2.M8 (GND[63]), U2.M10 (GND[63]), U2.M14 (GND[63]), U2.M18 (GND[63]), U2.N1 (GND[63]), U2.N9 (GND[63]), U2.N13 (GND[63]), U2.N21 (GND[63]), U2.P4 (GND[63]), U2.P8 (GND[63]), U2.P10 (GND[63]), U2.P12 (GND[63]), U2.P14 (GND[63]), U2.R9 (GND[63]), U2.R11 (GND[63]), U2.R13 (GND[63]), U2.R17 (GND[63]), U2.T20 (GND[63]), U2.U3 (GND[63]), U2.U13 (GND[63]), U2.V6 (GND[63]), U2.V16 (GND[63]), U2.W9 (GND[63]), U2.W19 (GND[63]), U2.Y2 (GND[63]), U2.Y12 (GND[63]), U2.Y22 (GND[63]), U3.2 (GND), U4.2 (GND), U5.2 (GND), U6.3 (GND), U7.2 (GND); also elsewhere on the board
unnamed: D1.2 (A), R9.2
unnamed: D1.1 (K), Q1.3 (D)
unnamed: D2.2 (A), R17.2
unnamed: D2.1 (K), Q2.3 (D)
unnamed: D3.2 (A), R20.2
unnamed: D4.2 (A), R21.2
unnamed: R2.2, R3.1, U1.6 (FB)
unnamed: L1.1, U1.3 (SW)
unnamed: C17.1, C18.1, FB1.2, U2.H10 (VCCPLL)
unnamed: R5.2, R6.1, U3.6 (FB)
unnamed: L2.1, U3.3 (SW)
unnamed: R8.2, R10.1, U4.6 (FB)
unnamed: L3.1, U4.3 (SW)
unnamed: R13.2, R16.1, U5.6 (FB)
unnamed: L4.1, U5.3 (SW)
unnamed: R15.2, U6.4 (PFI)
unnamed: R14.2, SW1.1, U6.1 (~MR)
unnamed: R18.2, R22.1, U7.6 (FB)
unnamed: L5.1, U7.3 (SW)
PGOOD_ALL: Q2.1 (G), R19.2, U5.5 (PG), U7.5 (PG)
POR: Q1.1 (G), R11.2, U6.7 (~RESET); also elsewhere on the board

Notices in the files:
UZAB.kicad_pcb:
(c) 2025 hnch@gmx.net DC4HP
CC BY-SA 4.0
